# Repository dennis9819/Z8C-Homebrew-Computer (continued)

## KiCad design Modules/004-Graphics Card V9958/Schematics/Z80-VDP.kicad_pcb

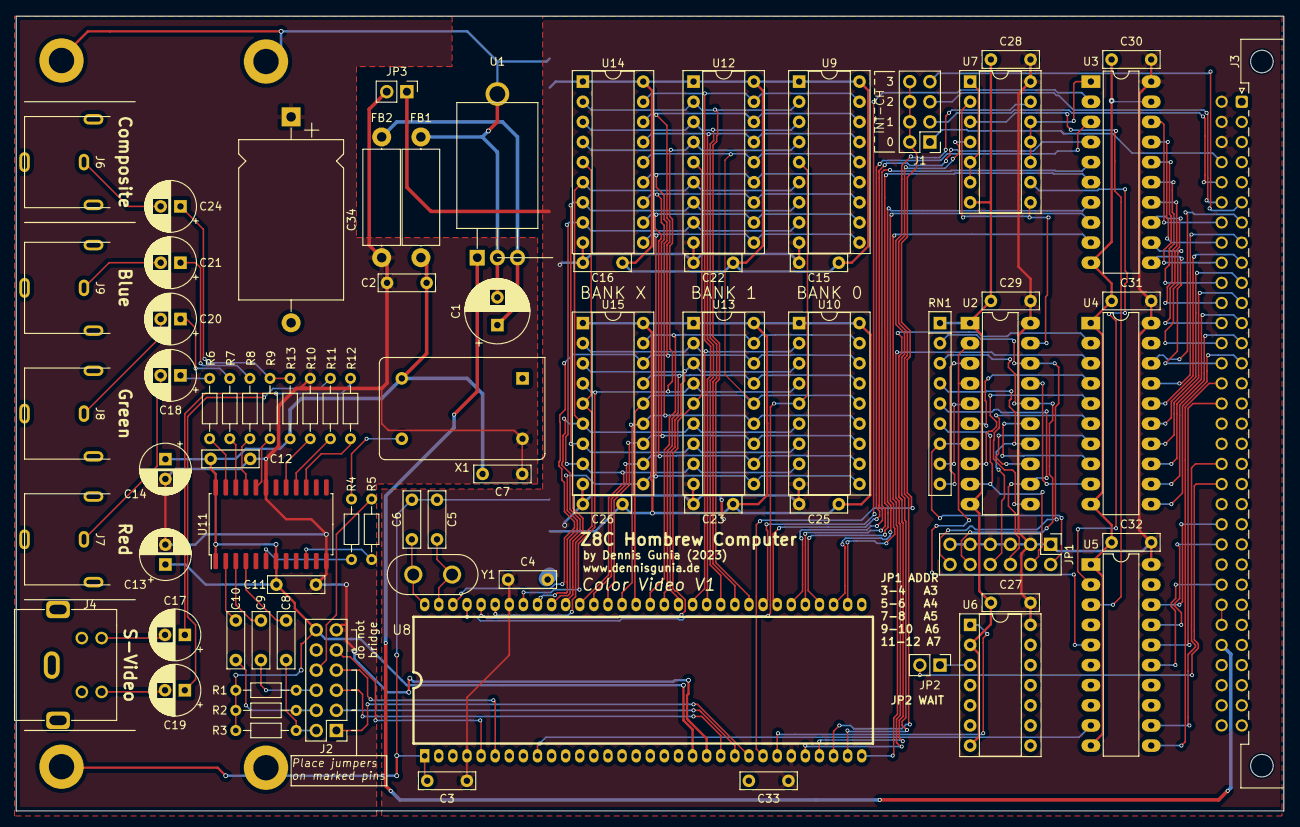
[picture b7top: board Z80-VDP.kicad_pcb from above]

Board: 4 copper layers, 160.0 x 100.3 mm, 78 parts (0 on the bottom side), 127 nets.

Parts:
C1: 470uF; CP_Radial_D8.0mm_P3.50mm
C2, C3, C4, C7, C8, C9, C10, C11, C12, C15, C16, C22, C23, C25, C26, C27, C28, C29, C30, C31, C32, C33: 100nF; C_Rect_L7.0mm_W2.0mm_P5.00mm
C5, C6: 22pF; C_Rect_L7.0mm_W2.0mm_P5.00mm
C13, C14: 47uF; CP_Radial_D6.3mm_P2.50mm
C17, C18, C19, C20, C21, C24: 220uF; CP_Radial_D6.3mm_P2.50mm
C34: 2200uF; CP_Axial_L20.0mm_D13.0mm_P26.00mm_Horizontal
FB1, FB2: FerriteBead; R_Axial_DIN0414_L11.9mm_D4.5mm_P15.24mm_Horizontal
J1: Conn_02x04_Odd_Even; PinHeader_2x04_P2.54mm_Vertical
J2: Conn_02x05_Counter_Clockwise; PinHeader_2x06_P2.54mm_Vertical
J3: Z8C_Card; Z8C Card
J4: S-VIDEO Out; MINIDIN4_SVIDEO
J6: Composite Out; RCA_Reichelt
J7: RGBOut_Red; RCA_Reichelt
J8: RGBOut_Green; RCA_Reichelt
J9: RGBOut_Blue; RCA_Reichelt
JP1: Conn_02x06_Odd_Even; PinHeader_2x06_P2.54mm_Vertical
JP2, JP3: JUMPER; PinHeader_1x02_P2.54mm_Vertical
R1, R2, R3: 470R; R_Axial_DIN0204_L3.6mm_D1.6mm_P7.62mm_Horizontal
R4, R5: 2k2; R_Axial_DIN0204_L3.6mm_D1.6mm_P7.62mm_Horizontal
R6, R7, R8, R11, R12: 75; R_Axial_DIN0204_L3.6mm_D1.6mm_P7.62mm_Horizontal
R9: 43; R_Axial_DIN0204_L3.6mm_D1.6mm_P7.62mm_Horizontal
R10: 2k61; R_Axial_DIN0204_L3.6mm_D1.6mm_P7.62mm_Horizontal
R13: 240; R_Axial_DIN0204_L3.6mm_D1.6mm_P7.62mm_Horizontal
RN1: R_Network08; R_Array_SIP9
U1: L7805; TO-220-3_Horizontal_TabDown
U2: 74LS688; DIP-20_W7.62mm_LongPads
U3, U4, U5: 74HC245; DIP-20_W7.62mm_LongPads
U6: 74HC125; DIP-14_W7.62mm_Socket
U7: 74HC02; DIP-14_W7.62mm_Socket
U8: V9958; SDIP64
U9, U10, U12, U13, U14, U15: 41464; DIP-18_W7.62mm_Socket
U11: CXA2075M; SOIC-24W_7.5x15.4mm_P1.27mm
X1: ACO-xxxMHz; Oscillator_DIP-14
Y1: 21.477MHz; Crystal_HC50_Vertical

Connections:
+5V: C3.1, C4.1, C15.1, C16.1, C22.1, C23.1, C25.1, C26.1, C27.1, C28.1, C29.1, C30.1, C31.1, C32.1, C33.1, J3.b1 (+5V), J3.b2 (+5V), J3.b3 (+5V), JP1.1, JP1.3, JP1.5, JP1.7, JP1.9, JP1.11, JP3.1, U2.20 (VCC), U3.20 (VCC), U4.20 (VCC), U5.20 (VCC), U6.14 (VCC), U7.14 (VCC), U8.4 (VRESET), U8.27 (/HRESET), U8.58 (VCC), U9.9 (VCC), U10.9 (VCC), U12.9 (VCC), U13.9 (VCC), U14.9 (VCC), U15.9 (VCC)
+5VA: C2.1, C7.1, C11.1, C12.1, C13.2, C14.2, C34.1, FB2.2, J2.11, JP3.2, R10.2, U8.21 (VCC/DAC), U11.12 (VCC1), U11.19 (VCC2), X1.14 (Vcc)
+12V: J3.b28 (+12V), U1.1 (IN)
/#A0: U4.2 (A0), U8.29 (MODE0)
/#A1: U4.3 (A1), U8.28 (MODE1)
/#A2: U2.6 (P2), U4.4 (A2)
/#A3: U2.8 (P3), U4.5 (A3)
/#A4: U2.11 (P4), U4.6 (A4)
/#A5: U2.13 (P5), U4.7 (A5)
/#A6: U2.15 (P6), U4.8 (A6)
/#A7: U2.17 (P7), U4.9 (A7)
/#D0: U3.2 (A0), U8.40 (D0)
/#D1: U3.3 (A1), U8.39 (D1)
/#D2: U3.4 (A2), U8.38 (D2)
/#D3: U3.5 (A3), U8.37 (D3)
/#D4: U3.6 (A4), U8.36 (D4)
/#D5: U3.7 (A5), U8.35 (D5)
/#D6: U3.8 (A6), U8.34 (D6)
/#D7: U3.9 (A7), U8.32 (D7)
/A0: J3.a7 (CA0), U4.18 (B0)
/A1: J3.a8 (CA1), U4.17 (B1)
/A2: J3.a9 (CA2), U4.16 (B2)
/A3: J3.a10 (CA3), U4.15 (B3)
/A4: J3.a11 (CA4), U4.14 (B4)
/A5: J3.a12 (CA5), U4.13 (B5)
/A6: J3.a13 (CA6), U4.12 (B6)
/A7: J3.a14 (CA7), U4.11 (B7)
/AD0: U8.49 (AD0), U9.14 (A0), U10.14 (A0), U12.14 (A0), U13.14 (A0), U14.14 (A0), U15.14 (A0)
/AD1: U8.50 (AD1), U9.13 (A1), U10.13 (A1), U12.13 (A1), U13.13 (A1), U14.13 (A1), U15.13 (A1)
/AD2: U8.51 (AD2), U9.12 (A2), U10.12 (A2), U12.12 (A2), U13.12 (A2), U14.12 (A2), U15.12 (A2)
/AD3: U8.52 (AD3), U9.11 (A3), U10.11 (A3), U12.11 (A3), U13.11 (A3), U14.11 (A3), U15.11 (A3)
/AD4: U8.53 (AD4), U9.8 (A4), U10.8 (A4), U12.8 (A4), U13.8 (A4), U14.8 (A4), U15.8 (A4)
/AD5: U8.54 (AD5), U9.7 (A5), U10.7 (A5), U12.7 (A5), U13.7 (A5), U14.7 (A5), U15.7 (A5)
/AD6: U8.55 (AD6), U9.6 (A6), U10.6 (A6), U12.6 (A6), U13.6 (A6), U14.6 (A6), U15.6 (A6)
/AD7: U8.56 (AD7), U9.10 (A7), U10.10 (A7), U12.10 (A7), U13.10 (A7), U14.10 (A7), U15.10 (A7)
/CLK_CPU: J3.b16 (CLK), U5.16 (B2)
/CSYNC: J2.7, U8.6 (CSYNC)
/D0: J3.b7 (CD0), U3.18 (B0)
/D1: J3.b8 (CD1), U3.17 (B1)
/D2: J3.b9 (CD2), U3.16 (B2)
/D3: J3.b10 (CD3), U3.15 (B3)
/D4: J3.b11 (CD4), U3.14 (B4)
/D5: J3.b12 (CD5), U3.13 (B5)
/D6: J3.b13 (CD6), U3.12 (B6)
/D7: J3.b14 (CD7), U3.11 (B7)
/HSYNC: J2.9, U8.5 (HSYNC)
/RD0: U8.41 (RD0), U9.2 (D0), U12.2 (D0), U14.2 (D0)
/RD1: U8.42 (RD1), U9.3 (D1), U12.3 (D1), U14.3 (D1)
/RD2: U8.43 (RD2), U9.15 (D2), U12.15 (D2), U14.15 (D2)
/RD3: U8.44 (RD3), U9.17 (D3), U12.17 (D3), U14.17 (D3)
/RD4: U8.45 (RD4), U10.2 (D0), U13.2 (D0), U15.2 (D0)
/RD5: U8.46 (RD5), U10.3 (D1), U13.3 (D1), U15.3 (D1)
/RD6: U8.47 (RD6), U10.15 (D2), U13.15 (D2), U15.15 (D2)
/RD7: U8.48 (RD7), U10.17 (D3), U13.17 (D3), U15.17 (D3)
/RGB_B: J2.1, U8.24 (B)
/RGB_G: J2.5, U8.22 (G)
/RGB_R: J2.3, U8.23 (R)
/R/W: U8.57 (R/W), U9.4 (~W), U10.4 (~W), U12.4 (~W), U13.4 (~W), U14.4 (~W), U15.4 (~W)
/VO_BLUE: C21.2, J9.1 (In)
/VO_COM: C24.2, J6.1 (In)
/VO_GREEN: C20.2, J8.1 (In)
/VO_RED: C18.2, J7.1 (In)
//CAS0: U8.61 (/CAS0), U9.5 (~RAS), U10.5 (~RAS)
//CAS1: U8.60 (/CAS1), U12.5 (~RAS), U13.5 (~RAS)
//CASX: U8.59 (/CAS_X), U14.5 (~RAS), U15.5 (~RAS)
//RAS: U8.62 (/RAS), U9.16 (~CAS), U10.16 (~CAS), U12.16 (~CAS), U13.16 (~CAS), U14.16 (~CAS), U15.16 (~CAS)
/~#IOREQ: U2.2 (P0), U2.4 (P1), U5.5 (A3)
/~#RD: U5.2 (A0), U7.9
/~#RESET: U5.9 (A7), U8.9 (/RESET)
/~#WAIT: U6.1, U8.26 (/WAIT)
/~#WR: U5.3 (A1), U7.3
/~INT0: J1.1, J3.b4 (~INT0)
/~INT1: J1.3, J3.b5 (~INT1)
/~INT2: J1.5, J3.b6 (~INT2)
/~INT3: J1.7, J3.a6 (~INT3)
/~IOREQ: J3.b25 (~IOREQ), U5.15 (B3)
/~IRQ_OUT: J1.2, J1.4, J1.6, J1.8, U8.25 (/INT)
/~M1: J3.b19 (~M1), U5.12 (B6)
/~RD: J3.b22 (~RD), U5.18 (B0)
/~RESET: J3.b15 (~RESET), U5.11 (B7)
/~VDP_RD: U7.13, U8.31 (/CSR)
/~VDP_WR: U7.4, U8.30 (/CSW)
/~WAIT: J3.b20 (~WAIT), JP2.2
/~WR: J3.b23 (~WR), U5.17 (B1)
BUSDIR: U3.1 (A->B), U7.10, U7.11, U7.12
GND: C1.2, C3.2, C4.2, C5.2, C6.1, C15.2, C16.2, C22.2, C23.2, C25.2, C26.2, C27.2, C28.2, C29.2, C30.2, C31.2, C32.2, C33.2, FB1.1, J3.G (CHASSIS), J3.a1 (GND), J3.a2 (GND), J3.a3 (GND), J3.a4 (GND), J3.b32 (GND), RN1.1 (common), U1.2 (GND), U2.1 (G), U2.10 (GND), U3.10 (GND), U3.19 (CE), U4.1 (A->B), U4.10 (GND), U4.19 (CE), U5.1 (A->B), U5.10 (GND), U5.13 (B5), U5.14 (B4), U5.19 (CE), U6.2, U6.4, U6.5, U6.7 (GND), U6.9, U6.10, U6.12, U6.13, U7.7 (GND), U8.1 (GND), U9.1 (~OE), U9.18 (GND), U10.1 (~OE), U10.18 (GND), U12.1 (~OE), U12.18 (GND), U13.1 (~OE), U13.18 (GND), U14.1 (~OE), U14.18 (GND), U15.1 (~OE), U15.18 (GND)
GNDA: C2.2, C7.2, C11.2, C12.2, C13.1, C14.1, C34.2, FB1.2, J2.12, J4.1, J4.2, J4.G, J6.2 (Ext), J7.2 (Ext), J8.2 (Ext), J9.2 (Ext), R1.1, R2.1, R3.1, R13.1, U8.20 (GND/DAC), U11.1 (GND1), U11.7 (NPIN), U11.24 (GND2), X1.7 (GND)
unnamed: C17.1, R12.2
unnamed: C17.2, J4.4
unnamed: C18.1, R6.2
unnamed: C19.1, R11.2
unnamed: C19.2, J4.3
unnamed: C20.1, R7.2
unnamed: C21.1, R8.2
unnamed: C24.1, R9.2, R13.2
unnamed: C8.1, J2.2, R3.2
unnamed: C10.1, J2.4, R2.2
unnamed: C9.1, J2.6, R1.2
unnamed: J2.8, R5.1
unnamed: J3.b26 (IEI), J3.b27 (IEO)
unnamed: JP1.2, RN1.7 (R6), U2.7 (R2)
unnamed: JP1.4, RN1.6 (R5), U2.9 (R3)
unnamed: JP1.6, RN1.5 (R4), U2.12 (R4)
unnamed: JP1.8, RN1.4 (R3), U2.14 (R5)
unnamed: JP1.10, RN1.3 (R2), U2.16 (R6)
unnamed: JP1.12, RN1.2 (R1), U2.18 (R7)
unnamed: JP2.1, U6.3
unnamed: RN1.8 (R7), U2.5 (R1)
unnamed: RN1.9 (R8), U2.3 (R0)
unnamed: C1.1, FB2.1, U1.3 (OUT)
unnamed: U2.19 (P=R), U7.2, U7.8
unnamed: U7.1, U7.5, U7.6
unnamed: C5.1, U8.63 (XTAL1), Y1.1
unnamed: C6.2, U8.64 (XTAL2), Y1.2
unnamed: C8.2, U11.4 (BIN)
unnamed: R8.1, U11.21 (BOUT)
unnamed: R12.1, U11.15 (COUT)
unnamed: R9.1, U11.20 (CVOUT)
unnamed: C9.2, U11.3 (GIN)
unnamed: R7.1, U11.22 (GOUT)
unnamed: C10.2, U11.2 (RIN)
unnamed: R6.1, U11.23 (ROUT)
unnamed: R4.2, U11.6 (SCIN)
unnamed: R5.2, U11.10 (SYNCIN)
unnamed: R11.1, U11.16 (YOUT)
unnamed: R10.1, U11.17 (YTRAP)
unnamed: R4.1, X1.8 (OUT)

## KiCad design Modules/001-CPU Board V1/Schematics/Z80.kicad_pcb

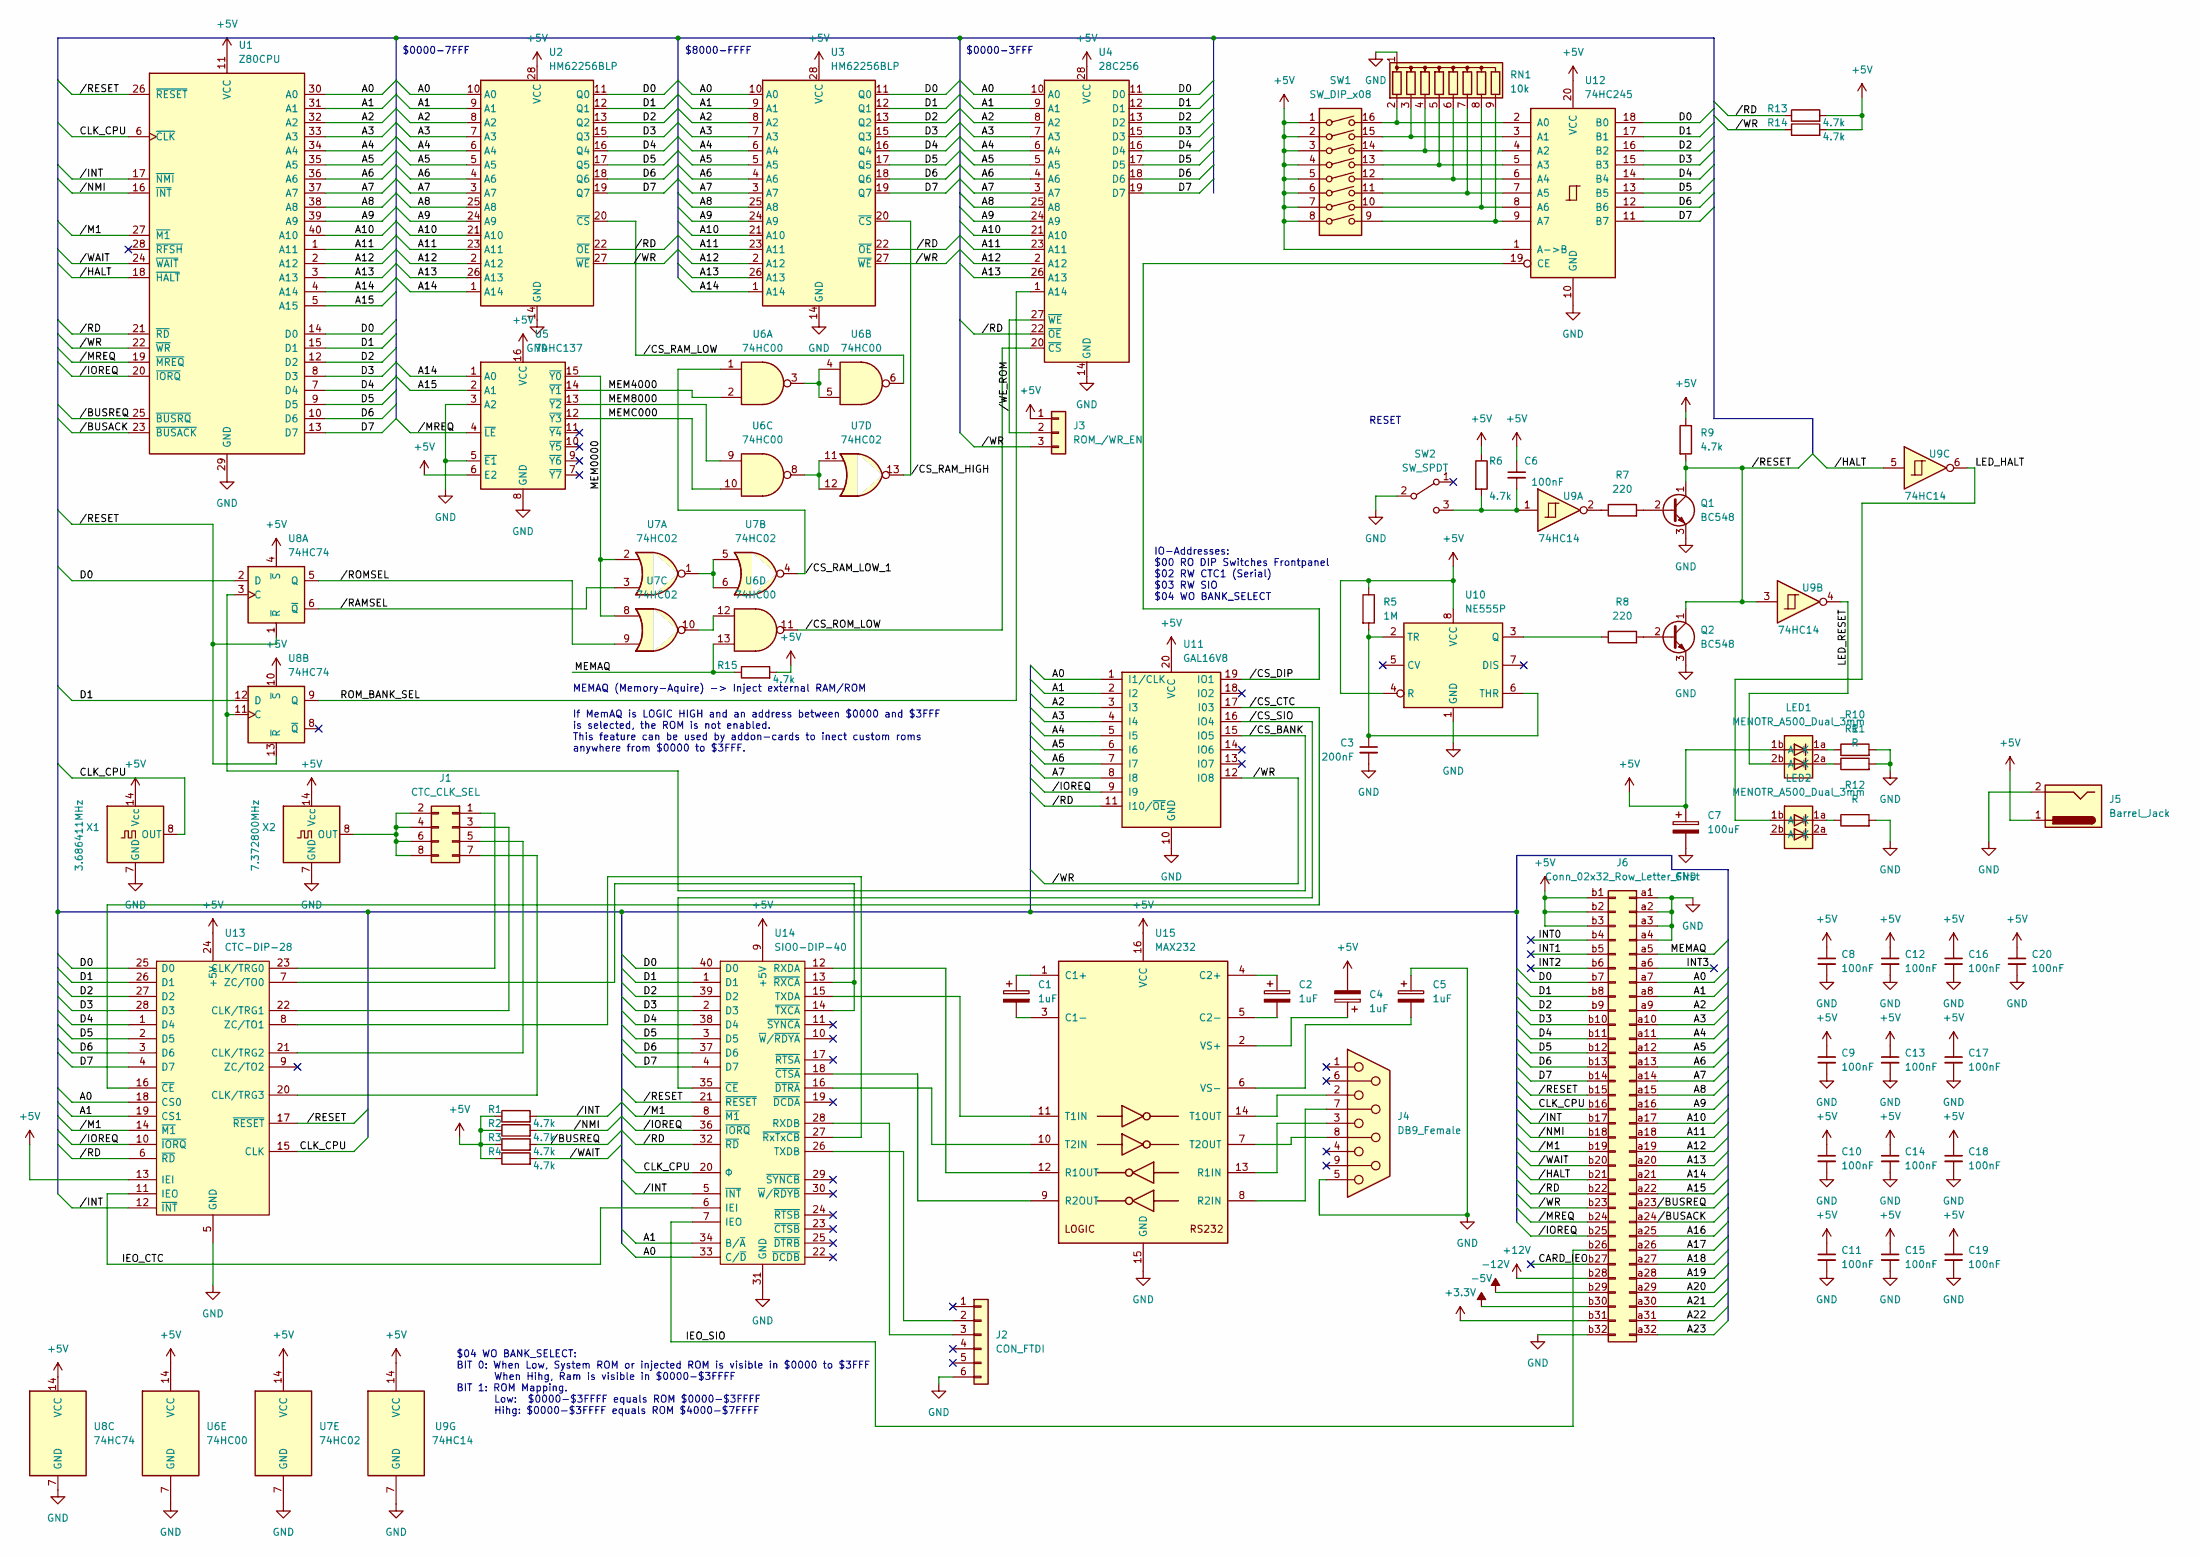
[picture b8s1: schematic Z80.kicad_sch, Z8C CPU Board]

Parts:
C1, C2, C4, C5: 1uF; CP_Radial_D6.3mm_P2.50mm
C3: 200nF; C_Rect_L7.0mm_W2.0mm_P5.00mm
C6, C8, C9, C10, C11, C12, C13, C14, C15, C16, C17, C18, C19, C20: 100nF; C_Rect_L7.0mm_W2.0mm_P5.00mm
C7: 100uF; CP_Radial_D8.0mm_P2.50mm
J1: CTC_CLK_SEL; PinHeader_2x04_P2.54mm_Vertical
J2: CON_FTDI; PinSocket_1x06_P2.54mm_Vertical
J3: ROM_/WR_EN; PinHeader_1x03_P2.54mm_Vertical
J4: DB9_Female; DSUB-9_Female_Horizontal_P2.77x2.84mm_EdgePinOffset9.90mm_H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
J5: Barrel_Jack; Barrel_Jack_5.5mmODx2.1mmID_PJ-202A
J6: Conn_02x32_Row_Letter_First; DIN41612_Q_2x32_Male_Horizontal_THT
LED1, LED2: MENOTR_A500_Dual_3mm; MENTOR A500 Dual 3mm
Q1, Q2: BC548; TO-92_Inline
R1, R2, R3, R4, R6, R9, R13, R14, R15: 4.7k; R_Axial_DIN0204_L3.6mm_D1.6mm_P2.54mm_Vertical
R5: 1M; R_Axial_DIN0204_L3.6mm_D1.6mm_P2.54mm_Vertical
R7, R8: 220; R_Axial_DIN0204_L3.6mm_D1.6mm_P2.54mm_Vertical
R10, R11, R12: R; R_Axial_DIN0204_L3.6mm_D1.6mm_P2.54mm_Vertical
RN1: 10k; R_Array_SIP9
SW1: SW_DIP_x08; SW_DIP_SPSTx08_Piano_CTS_Series194-8MSTN_W7.62mm_P2.54mm
SW2: SW_SPDT; Toggle_Switch_100SP1T2B4M6QE
U1: Z80CPU; DIP-40_W15.24mm_Socket_LongPads
U2, U3: HM62256BLP; DIP-28_W7.62mm_Socket_LongPads
U4: 28C256; DIP_Socket-28_W11.9_W12.7_W15.24_W17.78_W18.5_3M_228-1277-0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
U5: 74HC137; DIP-16_W7.62mm_Socket_LongPads
U6: 74HC00; DIP-14_W7.62mm_Socket_LongPads
U7: 74HC02; DIP-14_W7.62mm_Socket_LongPads
U8: 74HC74; DIP-14_W7.62mm_Socket_LongPads
U9: 74HC14; DIP-14_W7.62mm_Socket_LongPads
U10: NE555P; DIP-8_W7.62mm_Socket_LongPads
U11: GAL16V8; DIP-20_W7.62mm_Socket_LongPads
U12: 74HC245; DIP-20_W7.62mm_Socket_LongPads
U13: CTC-DIP-28; DIP-28_W15.24mm_Socket_LongPads; Manufacturer_Part_Number Z84C3010PEG; Mouser Part Number 692-Z84C3010PEG
U14: SIO0-DIP-40; DIP-40_W15.24mm_Socket_LongPads; Manufacturer_Part_Number Z84C4206PEG; Mouser Part Number 692-Z84C4206PEG
U15: MAX232; DIP-16_W7.62mm_Socket_LongPads
X1: 3.686411MHz; Oscillator_DIP-14
X2: 7.372800MHz; Oscillator_DIP-14

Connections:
+3V3: J6.b31
+5V: C4.2, C6.1, C7.1, C8.1, C9.1, C10.1, C11.1, C12.1, C13.1, C14.1, C15.1, C16.1, C17.1, C18.1, C19.1, C20.1, J3.1, J5.1, J6.b1, J6.b2, J6.b3, LED1.1b (A), R1.1, R2.1, R3.1, R4.1, R5.1, R6.1, R9.1, R13.2, R14.2, R15.2, SW1.1, SW1.2, SW1.3, SW1.4, SW1.5, SW1.6, SW1.7, SW1.8, U1.11 (VCC), U2.28 (VCC), U3.28 (VCC), U4.28 (VCC), U5.6 (E2), U5.16 (VCC), U6.14 (VCC), U7.14 (VCC), U8.4 (~S), U8.10 (~S), U8.14 (VCC), U9.14 (VCC), U10.4 (R), U10.8 (VCC), U11.20 (VCC), U12.1 (A->B), U12.20 (VCC), U13.13 (IEI), U13.24 (+5V), U14.9 (+5V), U15.16 (VCC), X1.14 (Vcc), X2.14 (Vcc)
+12V: J6.b28
-5V: J6.b30
-12V: J6.b29
/A0: J6.a7, U1.30 (A0), U2.10 (A0), U3.10 (A0), U4.10 (A0), U11.1 (I1/CLK), U13.18 (CS0), U14.33 (C/~D)
/A1: J6.a8, U1.31 (A1), U2.9 (A1), U3.9 (A1), U4.9 (A1), U11.2 (I2), U13.19 (CS1), U14.34 (B/~A)
/A2: J6.a9, U1.32 (A2), U2.8 (A2), U3.8 (A2), U4.8 (A2), U11.3 (I3)
/A3: J6.a10, U1.33 (A3), U2.7 (A3), U3.7 (A3), U4.7 (A3), U11.4 (I4)
/A4: J6.a11, U1.34 (A4), U2.6 (A4), U3.6 (A4), U4.6 (A4), U11.5 (I5)
/A5: J6.a12, U1.35 (A5), U2.5 (A5), U3.5 (A5), U4.5 (A5), U11.6 (I6)
/A6: J6.a13, U1.36 (A6), U2.4 (A6), U3.4 (A6), U4.4 (A6), U11.7 (I7)
/A7: J6.a14, U1.37 (A7), U2.3 (A7), U3.3 (A7), U4.3 (A7), U11.8 (I8)
/A8: J6.a15, U1.38 (A8), U2.25 (A8), U3.25 (A8), U4.25 (A8)
/A9: J6.a16, U1.39 (A9), U2.24 (A9), U3.24 (A9), U4.24 (A9)
/A10: J6.a17, U1.40 (A10), U2.21 (A10), U3.21 (A10), U4.21 (A10)
/A11: J6.a18, U1.1 (A11), U2.23 (A11), U3.23 (A11), U4.23 (A11)
/A12: J6.a19, U1.2 (A12), U2.2 (A12), U3.2 (A12), U4.2 (A12)
/A13: J6.a20, U1.3 (A13), U2.26 (A13), U3.26 (A13), U4.26 (A13)
/A14: J6.a21, U1.4 (A14), U2.1 (A14), U3.1 (A14), U5.1 (A0)
/A15: J6.a22, U1.5 (A15), U5.2 (A1)
/A16: J6.a25
/A17: J6.a26
/A18: J6.a27
/A19: J6.a28
/A20: J6.a29
/A21: J6.a30
/A22: J6.a31
/A23: J6.a32
/CARD_IEO: J6.b27
/CLK_CPU: J6.b16, U1.6 (~CLK), U13.15 (CLK), U14.20 (Φ), X1.8 (OUT)
/D0: J6.b7, U1.14 (D0), U2.11 (Q0), U3.11 (Q0), U4.11 (D0), U8.2 (D), U12.18 (B0), U13.25 (D0), U14.40 (D0)
/D1: J6.b8, U1.15 (D1), U2.12 (Q1), U3.12 (Q1), U4.12 (D1), U8.12 (D), U12.17 (B1), U13.26 (D1), U14.1 (D1)
/D2: J6.b9, U1.12 (D2), U2.13 (Q2), U3.13 (Q2), U4.13 (D2), U12.16 (B2), U13.27 (D2), U14.39 (D2)
/D3: J6.b10, U1.8 (D3), U2.15 (Q3), U3.15 (Q3), U4.15 (D3), U12.15 (B3), U13.28 (D3), U14.2 (D3)
/D4: J6.b11, U1.7 (D4), U2.16 (Q4), U3.16 (Q4), U4.16 (D4), U12.14 (B4), U13.1 (D4), U14.38 (D4)
/D5: J6.b12, U1.9 (D5), U2.17 (Q5), U3.17 (Q5), U4.17 (D5), U12.13 (B5), U13.2 (D5), U14.3 (D5)
/D6: J6.b13, U1.10 (D6), U2.18 (Q6), U3.18 (Q6), U4.18 (D6), U12.12 (B6), U13.3 (D6), U14.37 (D6)
/D7: J6.b14, U1.13 (D7), U2.19 (Q7), U3.19 (Q7), U4.19 (D7), U12.11 (B7), U13.4 (D7), U14.4 (D7)
/IEO_CTC: U13.11 (IEO), U14.6 (IEI)
/IEO_SIO: J6.b26, U14.7 (IEO)
/INT0: J6.b4
/INT1: J6.b5
/INT2: J6.b6
/INT3: J6.a6
/LED_HALT: LED2.1b (A), U9.6
/LED_RESET: LED1.2b (A), U9.4
/MEM0000: U5.15 (~Y0), U7.2, U7.8
/MEM4000: U5.14 (~Y1), U6.2
/MEM8000: U5.13 (~Y2), U6.9
/MEMAQ: J6.a5, R15.1, U6.13
/MEMC000: U5.12 (~Y3), U6.10
//BUSACK: J6.a24, U1.23 (~BUSACK)
//BUSREQ: J6.a23, R3.2, U1.25 (~BUSRQ)
//CS_BANK: U8.3 (C), U8.11 (C), U11.15 (IO5)
//CS_CTC: U11.17 (I03), U13.16 (~CE)
//CS_DIP: U11.19 (IO1), U12.19 (CE)
//CS_RAM_HIGH: U3.20 (~CS), U7.13
//CS_RAM_LOW: U2.20 (~CS), U6.6
//CS_RAM_LOW_1: U6.1, U7.4
//CS_SIO: U11.16 (IO4), U14.35 (~CE)
//HALT: J6.b21, U1.18 (~HALT), U9.5
//INT: J6.b17, R1.2, U1.17 (~NMI), U13.12 (~INT), U14.5 (~INT)
//IOREQ: J6.b25, U1.20 (~IORQ), U11.9 (I9), U13.10 (~IORQ), U14.36 (~IORQ)
//M1: J6.b19, U1.27 (~M1), U13.14 (~M1), U14.8 (~M1)
//MREQ: J6.b24, U1.19 (~MREQ), U5.4 (~LE)
//NMI: J6.b18, R2.2, U1.16 (~INT)
//RAMSEL: U7.3, U8.6 (~Q)
//RESET: J6.b15, Q1.1 (C), Q2.1 (C), R9.2, U1.26 (~RESET), U8.1 (~R), U8.13 (~R), U9.3, U13.17 (~RESET), U14.21 (~RESET)
//ROMSEL: U7.9, U8.5 (Q)
//WAIT: J6.b20, R4.2, U1.24 (~WAIT)
//WE_ROM: J3.2, U4.27 (~WE)
GND: C3.2, C5.1, C7.2, C8.2, C9.2, C10.2, C11.2, C12.2, C13.2, C14.2, C15.2, C16.2, C17.2, C18.2, C19.2, C20.2, J2.6, J4.5, J5.2, J6.a1, J6.a2, J6.a3, J6.a4, J6.b32, Q1.3 (E), Q2.3 (E), R10.2, R11.2, R12.2, RN1.1 (common), SW2.2 (B), U1.29 (GND), U2.14 (GND), U3.14 (GND), U4.14 (GND), U5.3 (A2), U5.5 (~E1), U5.8 (GND), U6.7 (GND), U7.7 (GND), U8.7 (GND), U9.7 (GND), U10.1 (GND), U11.10 (GND), U12.10 (GND), U13.5 (GND), U14.31 (GND), U15.15 (GND), X1.7 (GND), X2.7 (GND)
unnamed: C1.1, U15.1 (C1+)
unnamed: C1.2, U15.3 (C1-)
unnamed: C2.1, U15.4 (C2+)
unnamed: C2.2, U15.5 (C2-)
unnamed: C3.1, R5.2, U10.2 (TR), U10.6 (THR)
unnamed: C4.1, U15.2 (VS+)
unnamed: C5.2, U15.6 (VS-)
unnamed: C6.2, R6.2, SW2.3 (C), U9.1
unnamed: J1.1, U13.23 (CLK/TRG0)
unnamed: J1.2, J1.4, J1.6, J1.8, X2.8 (OUT)
unnamed: J1.3, U13.22 (CLK/TRG1)
unnamed: J1.5, U13.21 (CLK/TRG2)
unnamed: J1.7, U13.20 (CLK/TRG3)
unnamed: J2.2, U14.26 (TXDB)
unnamed: J2.3, U14.28 (RXDB)
unnamed: J4.2, U15.14 (T1OUT)
unnamed: J4.3, U15.13 (R1IN)
unnamed: J4.7, U15.8 (R2IN)
unnamed: J4.8, U15.7 (T2OUT)
unnamed: LED1.1a (K), R10.1
unnamed: LED1.2a (K), R11.1
unnamed: LED2.1a (K), R12.1
unnamed: Q1.2 (B), R7.2
unnamed: Q2.2 (B), R8.2
unnamed: R7.1, U9.2
unnamed: R8.1, U10.3 (Q)
unnamed: RN1.2 (R1), SW1.16, U12.2 (A0)
unnamed: RN1.3 (R2), SW1.15, U12.3 (A1)
unnamed: RN1.4 (R3), SW1.14, U12.4 (A2)
unnamed: RN1.5 (R4), SW1.13, U12.5 (A3)
unnamed: RN1.6 (R5), SW1.12, U12.6 (A4)
unnamed: RN1.7 (R6), SW1.11, U12.7 (A5)
unnamed: RN1.8 (R7), SW1.10, U12.8 (A6)
unnamed: RN1.9 (R8), SW1.9, U12.9 (A7)
unnamed: U6.3, U6.4, U6.5
unnamed: U6.8, U7.11, U7.12
unnamed: U7.1, U7.5, U7.6
unnamed: U6.12, U7.10
unnamed: U13.7 (ZC/TO0), U14.13 (~RXCA), U14.14 (~TXCA)
unnamed: U13.8 (ZC/TO1), U14.27 (~RxTxCB)
unnamed: U14.12 (RXDA), U15.12 (R1OUT)
unnamed: U14.15 (TXDA), U15.11 (T1IN)
unnamed: U14.16 (~DTRA), U15.10 (T2IN)
unnamed: U14.18 (~CTSA), U15.9 (R2OUT)

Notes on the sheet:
If MemAQ is LOGIC HIGH and an address between $0000 and $3FFF is selected, the ROM is not enabled. This feature can be used by addon-cards to inect custom roms anywhere from $0000 to $3FFF.
$0000-7FFF
$8000-FFFF
IO-Addresses: $00 RO DIP Switches Frontpanel $02 RW CTC1 (Serial) $03 RW SIO $04 WO BANK_SELECT
MEMAQ (Memory-Aquire) -> Inject external RAM/ROM
$04 WO BANK_SELECT: BIT 0: When Low, System ROM or injected ROM is visible in $0000 to $3FFF When Hihg, Ram is visible in $0000-$3FFFF BIT 1: ROM Mapping. Low: $0000-$3FFFF equals ROM $0000-$3FFFF Hihg: $0000-$3FFFF equals ROM $4000-$7FFFF
RESET
$0000-3FFF

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
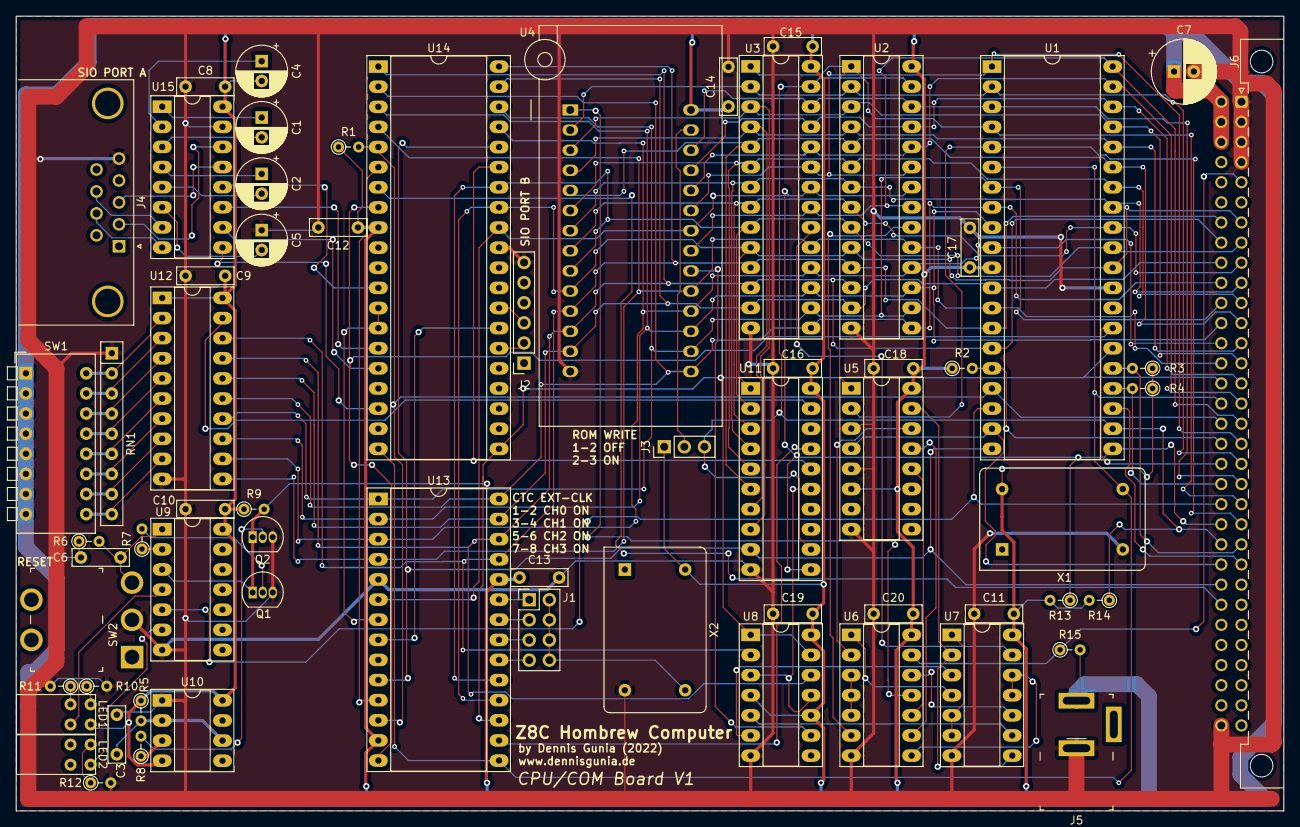
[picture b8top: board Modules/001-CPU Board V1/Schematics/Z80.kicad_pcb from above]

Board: 2 copper layers, 160.0 x 100.3 mm, 65 parts (0 on the bottom side), 104 nets.

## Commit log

2022-10-24 added files
2022-12-05 New features
2022-12-16 Added new Info
2022-12-20 added i2c controller tests
2023-01-16 added i2c controller functions, added IDE interface functions, fiexd IDE schematics
2023-12-26 restructure
2023-12-28 multiple updates
2024-01-12 progress on FAT16 support
2024-01-24 fat16 working
2024-06-24 pushed updates
2024-06-24 add datasheets
2024-06-24 reorganize everything
2024-11-30 several fixes
2024-12-22 fix Sound board rev1
2024-12-22 added updated schematics
2025-01-03 Added Backplane
